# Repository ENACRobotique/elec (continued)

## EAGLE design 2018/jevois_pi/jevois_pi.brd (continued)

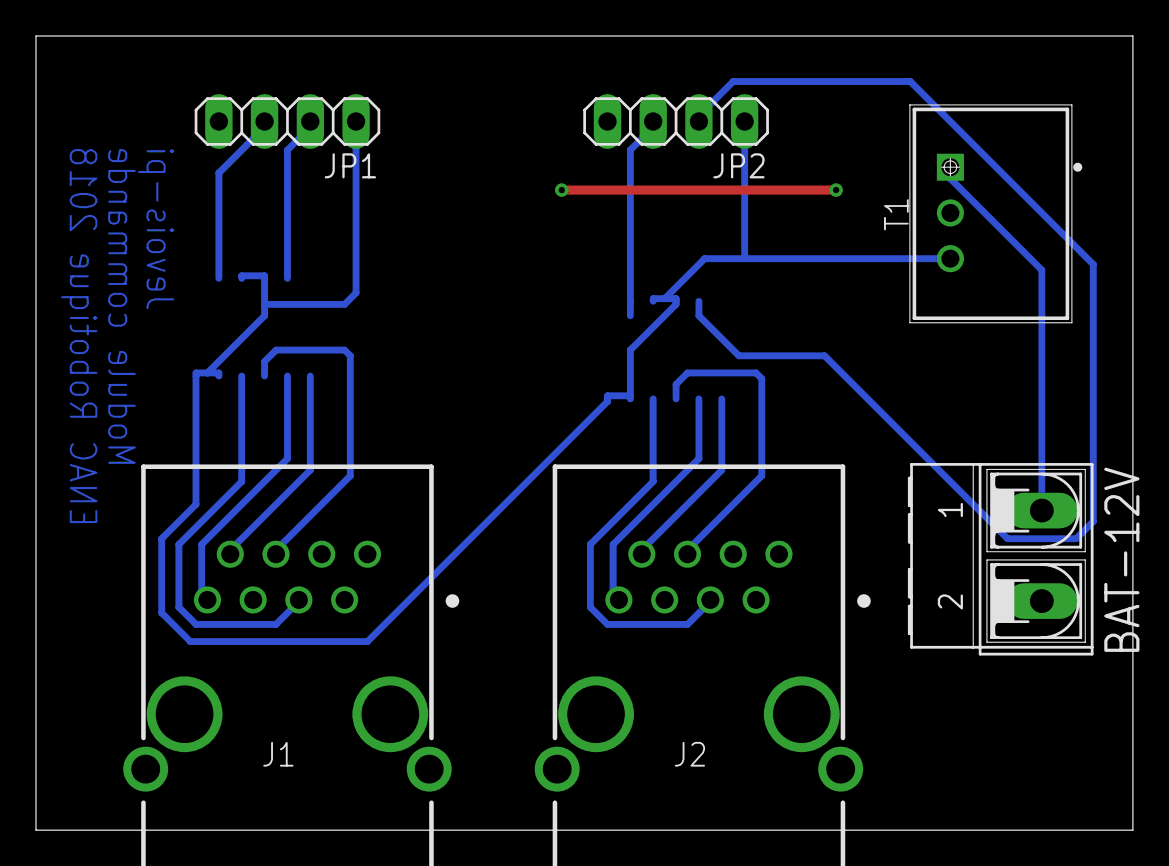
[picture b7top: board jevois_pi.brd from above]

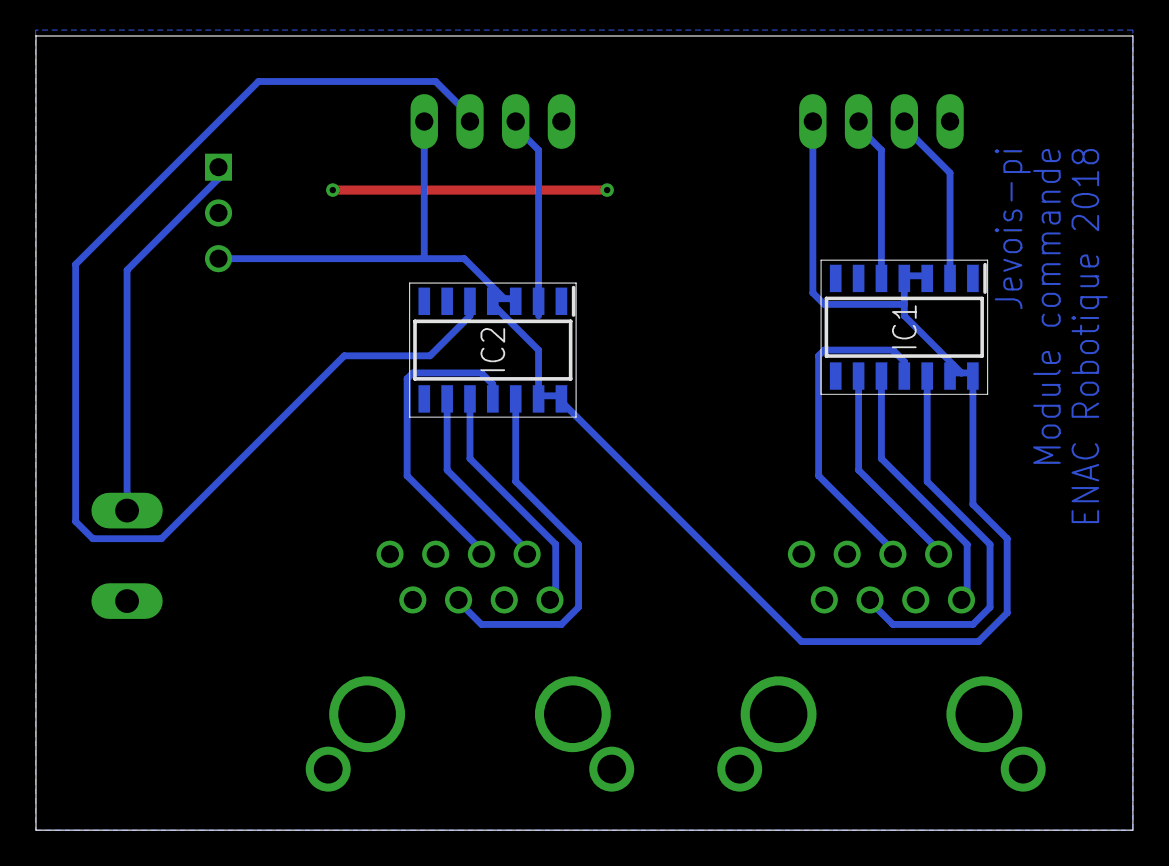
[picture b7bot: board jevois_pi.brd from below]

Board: 2 copper layers, 60.9 x 44.1 mm, 8 parts (2 on the bottom side), 15 nets.

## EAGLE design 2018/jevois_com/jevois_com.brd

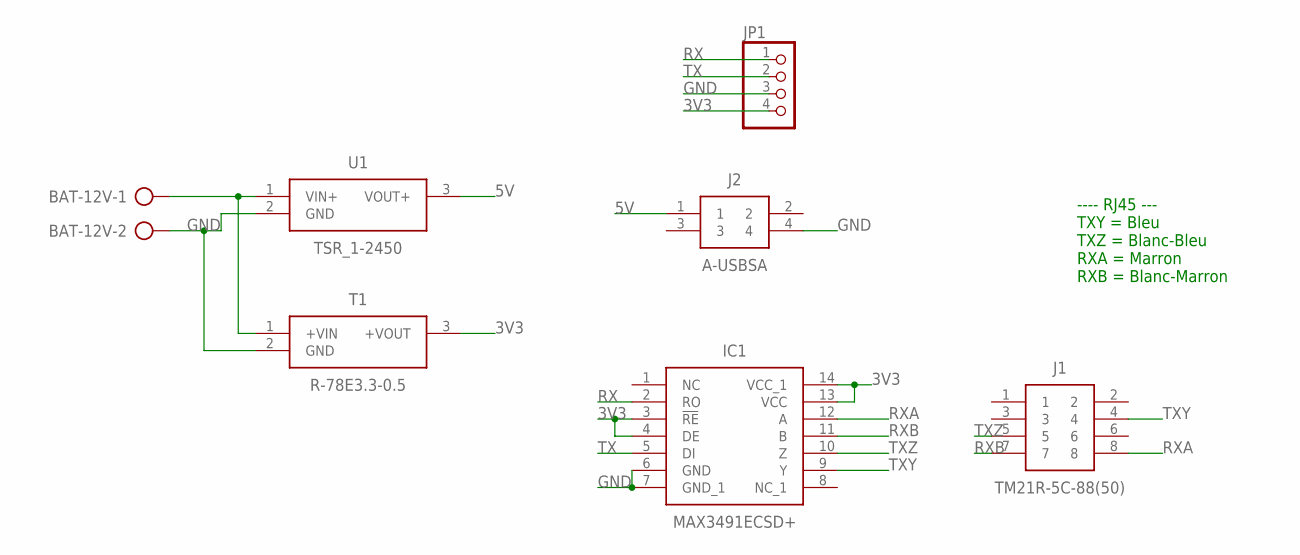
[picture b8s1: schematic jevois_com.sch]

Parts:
BAT-12V: AK500/2-H
IC1: MAX3491ECSD+; SOIC127P600X175-14N
J1: TM21R-5C-88(50)
J2: A-USBSA
JP1: PINHD-1X4; 1X04
T1: R-78E3.3-0.5; SHDRV3W100P0_254_1X3_1160X850X
U1: TSR_1-2450; TSR-1-24120

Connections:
3V3: IC1.3 (!RE), IC1.4 (DE), IC1.13 (VCC), IC1.14 (VCC_1), JP1.4, T1.3 (+VOUT)
5V: J2.1, U1.3 (VOUT+)
GND: BAT-12V.2, IC1.6 (GND), IC1.7 (GND_1), J2.4, JP1.3, T1.2 (GND), U1.2 (GND)
unnamed: BAT-12V.1, T1.1 (+VIN), U1.1 (VIN+)
RX: IC1.2 (RO), JP1.1
RXA: IC1.12 (A), J1.8
RXB: IC1.11 (B), J1.7
TX: IC1.5 (DI), JP1.2
TXY: IC1.9 (Y), J1.4
TXZ: IC1.10 (Z), J1.5

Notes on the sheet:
---- RJ45 --- TXY = Bleu TXZ = Blanc-Bleu RXA = Marron RXB = Blanc-Marron

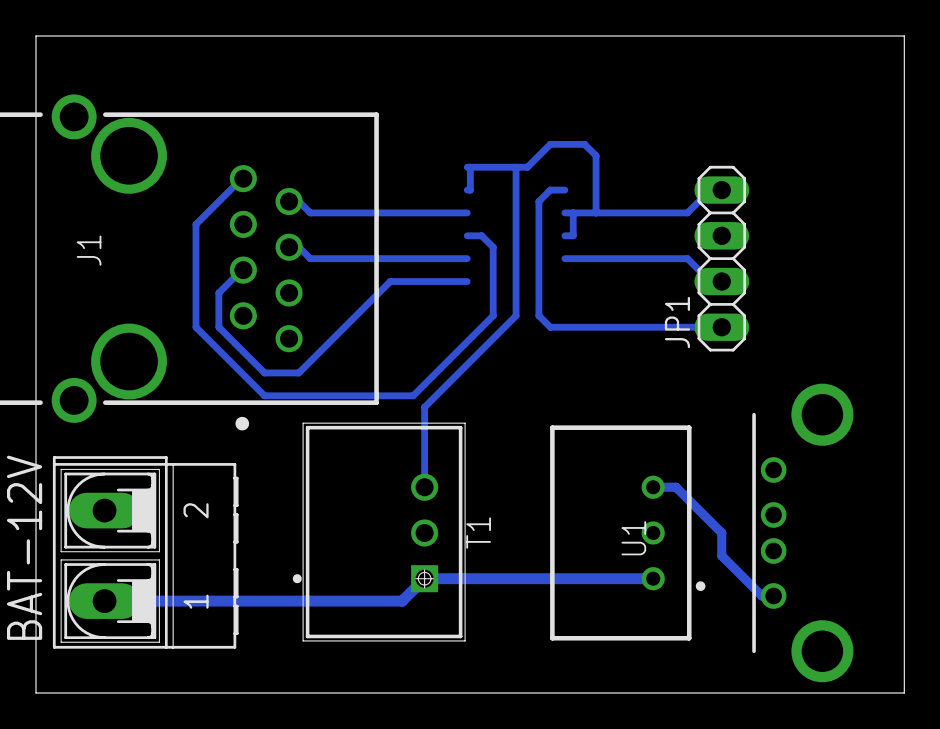
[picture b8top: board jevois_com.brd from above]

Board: 2 copper layers, 48.2 x 36.5 mm, 7 parts (1 on the bottom side), 10 nets.

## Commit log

2015-03-24 [primary_robot] Adds AI/IO board
2015-03-24 [primary_robot] Adds control + power boards Rev1
2015-03-24 [prop_tripod] Updates to pre-Rev2
2015-03-24 [prop-tripod] Update the footprint of the LPC, increase the readability of some name on the board
2015-03-25 [secondary_robot] Adds shematics and board
2015-03-25 [tester] adds shematics and board
2015-03-25 [secondary & tester] remove useless files and move bad located files
2015-03-27 [prop_tripod] Fixes RST connection
2015-04-01 [prop_tripod] Fixes buffer pull-ups + I²C pull-ups headers
2015-04-01 [prop_tripod] Removes useless buffer
2015-04-02 [prop_tripod] Changes pin asssignation
2015-04-03 [tester] add VCC pin for UART
2015-04-03 [tester] create ihm board
2015-04-04 [Programmer ICSP Atmega328p]
2015-04-04 [Programmer ICSP Atmega328p] smaller design
2015-04-04 Add gitignore to ignore .b#, .s#, pdf & epf files. Usefull for everyone.
2015-04-08 [Programmer ICSP Atmega328p] optimise routing
2015-04-08 [tester]move holes to make a good design
2015-04-14 [primary_robot] Adds C2014 R1 Arduino IO shield
2015-04-14 [priom/io] Updates some labels
2015-04-23 [primary_robot] Fixes Uart2 to Uart1 on the BBB
2015-05-05 [2014] Adds 2014 main elec
2015-05-17 [tester] modify to V2 Alpha.
2015-05-17 [tester] improve V2.
2015-05-17 [tester] add pins correspondance.
2015-05-18 [tester] add "pont diviseur" and some modification.
2015-05-21 [Arduino_like] add arduino like board.
2015-05-21 [Arduino_like] modify board.
2015-05-21 [Arduino_like] adds GND, VCC and AREF pins.
2015-05-31 [Arduino like] move on 0.1 inch grid.
2015-06-01 [Arduino like] align pins.
2015-06-01 [Arduino_like] align power.
2015-06-01 [arduino like] move via.
2015-06-01 [Arduino_like] add reset pin.
2015-06-01 [Arduino_like] move text.
2015-06-02 [Tester] new design.
2015-06-02 [tester] continue new design.
2015-06-02 [Arduino_like] change some dimensions.
2015-06-02 [tester] improve design.
2015-06-03 [Arduino_like] V0.1a
2015-06-03 [tester] V2.0a
2015-06-17 [Arduino_like] move labels to the right place.
2015-10-29 [Multitask attiny85] initial commit.
2015-10-29 [tester] modify pin configuration.
2015-10-30 [tester] Begin new design.
2015-10-30 [tester] finish design V3.
2015-10-30 [tester] improve 3rd design.
2015-10-30 [tester] add some measures.
2015-11-02 [tester] puts some wire in top.
2015-11-02 [tester] optimize some routes.
2015-11-02 [tester] keep separation between components.
2015-11-02 [tester] separate some vias.
2015-11-02 [tester] separate other routes.
2015-11-02 [Programmer ICSP Atmega328p] add capa values.
2015-11-03 [elec aiio] Adds a library with raspberry component
2015-11-03 [elec AIIO] Updates the old AIIO card to match the 2016 requirements, rasperry socket, IHM on ard, bluetooth socket on ard and 5 switch plugs on ard.
2016-02-11 [AIIO] Adds a reset button for the Raspi
2016-02-13 [AIIO_board] Add I2C bus "I2C0" for sonar sensors on shematic file.
2016-02-14 [AIIO board] Remove old .brd and .sch files.
2016-02-14 [AIIO boards] Put files in directories wrt the year.
2016-02-14 [AIIO_boards] Create and add components for IHM_BOARD.
2016-02-15 [AIIO_boards] Clean schematic and board files.
2016-02-15 [AIIO_boards] Update footprint of stage 4.
2016-02-15 [AIIO_board]Place connectors for sonar connectors.
2016-02-15 [AIIO_board]Place RP2 and make corrections on I2C_RP2 bus.
2016-02-16 [AIIO_boards] Connect servo connectors to PCA9685PW.
2016-02-16 [AIIO_board] Make route for sonar I2C
2016-02-16 [AIIO_board] Update pin Ardu
2016-02-16 [AIIO_boards] Route presence connectors.
2016-02-17 [AIIO_boars] Update footprint primary.
2016-02-17 [AIIO_board] Add I2C and UART connectors to Arduino and RP2 boards.
2016-02-17 [AIIO_boards] Add connectors for 5v_SIG and root them.
2016-02-17 [AIIO_board] Route IHM components.
2016-02-18 [AIIO_board] Add 3v3 reglator and connectors on .sch and .board files.
2016-02-21 [AIIO_board] Add button and connector for IHM. Remove useless pull-up resistors.
2016-02-22 [AIIO_board] Update personnal library for primary.
2016-02-22 [AIIO_board] Make correction on .brd file to avoid collsions btw parts.
2016-03-16 [AIIO boards] Make corrections, add components (board) for PCA9685.
2016-03-16 [Arm board] Add board for robotic arm.
2016-03-16 Add example file for CAM Processing (Gerber format).
2016-04-13 [AIIO 2016] Corrects a mistake (5V passing through Arduino A0)
2016-04-24 [Porgrammer ICSP] Make another design for handle Attiny85
2016-04-24 [Programmer ICSP] Add awesome eagle!
2016-09-07 [Programmer ICSP] Really add the eagle.
2016-09-07 [Color sensor] Add first version of color sensor.
2017-04-24 [primary] First 2017 commit.
2017-04-24 cleaning
2017-04-24 [Primary] Erase some componants.
2017-04-24 [primary] connectors board RPi.
2017-04-25 [primary] 2nd version, without mass plane.
2017-04-25 [primary] Adds mass plane.
2017-05-04 [RSPI] Adds schematic
2017-09-29 [Smarties_sorter] Adds schematic and board
2017-09-29 [Smarties_sorter] Adds flyback diode
2017-09-29 [Smarties Sorter] Adds a buck
2017-09-29 [Smarties sorter] Adds screw clamp for battery
2017-09-29 [Smarties Sorter] Adds ground plane.
2017-09-30 [Smarties Sorter] Connects AVCC to 5V + capacitor
2017-10-02 [Smarties_sorter] Change color sensor plug
2017-10-02 [Smarties_sorter] Adds resistor to pull down motor command
2017-10-02 [smarties_sorter] Adds UART plug
2017-10-02 [smarties_sorter] Adds capa on the motor
2017-10-02 [smarties_sorter] Change buck to ls7805 and route everything.
2017-10-06 [libraries] Move libraries to better named directory.
2017-10-06 [Multitask attiny85] Reduce wire width.
2017-10-27 [FAT board] Add schematic file.
2017-10-27 [FAT board] Add readme file.
2017-10-27 [FAT board] Modify specs a bit.
2017-10-27 [FAT board] Adds connector for free pins.
2017-10-27 [libraries] Adds 'diy-modules' library.
2017-10-27 [FAT board] Adds reset button.
2017-10-27 [FAT board] Adds necessary components for H-bridges.
2017-10-27 [FAT board] Change some names.
2017-10-27 [FAT board] Adds UART and I2C connectors.
2017-10-27 [FAT board] Connect motors to teensy and add dynamixel control.
2017-10-27 [FAT board] Adds power supply.
2017-10-27 [FAT board] Begin board.
2017-10-27 [primary] Adds label.
2017-10-27 [TRR] Adds board file.
2017-10-27 [TRR] Adds schematic for the car, TRR 2017.
2017-11-01 Add elec boards for primary robot.
2017-11-01 Complete previous commit.
2017-11-02 [FAT board] Connect additionnal power connectors behind interruptors.
2017-11-03 [FAT board] Route board.
2017-11-04 [FAT board] Correct shematic according to Melvin's comments.
2017-11-04 [FAT board] Modify board to match shematic correction.
2017-11-04 [FAT board] Adds some labels.
2017-11-04 Changed I2C Pull-Up resistor selector to match I2C specifications
    Note: I2C Resistors doesn't have any value yet. Assessment of line
    capacitance is in progress...
2017-11-05 Updated I2C ports and pull-up system to match I2C standard specifications
    Note : Assessment of Pull-Up resistors values is still pending.
2017-11-05 Simplified i2c pull-up selector and Partial routing (77%)
2017-11-06 Finished wiring using top layer jumpers
2017-11-07 Adding board Design Rules
2017-11-08 robot_base.sch/brd: routing complete, clearance increased and checked. Add teensy package with bigger pads.
2017-11-08 Change shape of the pads in a new package version of teensy
2017-11-08 Change shape of the pads for D24V50F5 (buck 5V)
2017-11-08 Update robot_system.sch/brd: Minor corrections in sch and start to route.
2017-11-09 Update and complete routing of robot_system board. Last checks TODO.
2017-11-16 Correction of traces Overlap issues
2017-11-23 [robot_base] Update robot_base and robot_systems boards.
2017-11-23 [robot_base] Update dimensions of robot_base board
2017-12-07 [robot_system] Increase clearance, update package of one condo
2017-12-07 [robot_base] Increase clearance
2017-12-10 [robot_base] Update clearance to 15 mil for wire, pad and via.
2017-12-10 [robot_base] Increase clearance. Better routing.
2017-12-11 Updated DRC file to current rules
2018-01-11 Adding Jevois Module transmission board + schematic
    To be set up on the remote modules
2018-01-11 Adding jevois command module and finishing boards
2018-01-11 Correcting a mismatch between input pins
2018-02-20 Adds librairies.
2018-02-20 [FAT pannal] Adds shematic and board.
2018-02-20 [FAT pannal] Split cavalier in two.
2018-02-21 [FAT pannal] Begins routing.
2018-02-21 [FAT pannal] Continue routing.
2018-02-22 [FAT pannal] Finish board V1.
2018-02-22 [FAT pannal] Adds pdfs.
2018-03-06 [dynamixel board] Adds dynamixel board V1.
2018-03-06 [FAT V2]Begin schematic
2018-03-12 [FAT] begins V2
2018-03-12 [Secondary] Adds the board.
2018-03-12 [secondary] Adds the final board
2018-03-12 [Secondary] Begining of the secondary elec card 2018
2018-03-12 [secondary 2018] Modificates the position of the elements above the x abscisse
2018-03-12 [Secondary] Finishes the 2018 schematic
2018-03-12 [secondary] Adds the final schematic and board
2018-03-12 [Libraries] Adds pth08080
2018-03-13 [FAT V2] Route easy side.
2018-03-13 [FAT V2] Finish board.
2018-10-05 Debut test motor control
2019-04-07 [principal2019] Footprint libs.
2019-04-07 [principal2019] Symbol libs.
2019-04-07 [principal2019] 3d packages.
2019-04-07 [principal2019] Adds project.
2019-04-08 [principal2019] Assigns footprints.
2019-04-10 [principal2019] End of elec.
2019-04-10 [principal2019] Adds lib.
2019-04-10 [principal2019] file .pro
2019-04-10 Adds credentials and PDF.
2020-02-12 Begins elec 2020 robot A.
2020-02-14 Updates elec RobotA2020.
2020-02-19 Adds phare2020 elec.
2020-02-27 finish schematic PCA9685 and robotA
2020-03-06 routing carte_PCA9685
2020-03-08 Correction cartes 2020 robotA
2020-03-12 Fin carte elec 2020 robot-a
2020-09-20 init folder and main card
    add folder for main card and kicad libs
2022-11-26 début carte alim v2
2022-11-26 CarteAlimV2-Suite et fin
2022-11-26 Ajout des libraries de logo
2023-02-02 Ajout des cartes de 2022 + début carte principale 2023
2023-02-02 Ajout de labels sur le schématique, tome1
2023-02-03 Ajout des drivers de steppers + connecté tous les tags
2023-02-08 Schéma carte principale fini
2023-02-08 Ajout de résistances de pullup
2023-02-11 Ajout de la carte du panier
2023-02-16 Suppression d'une carte foireuse
2023-02-16 Carte d'alim V2.5
2023-02-16 Arrondi d'une dernière piste
2023-02-16 arrondis ++
2023-02-16 MAJ cartes elec
2023-02-16 Update finale
2023-02-16 Fin de l'elec
2023-02-27 WARNING ENCODER 1
2025-01-30 [pami 2025] Fin PCB V1
2025-03-14 hub CAN
2025-03-17 Hub CAN WIp
2025-10-17 hub smart servos
2025-10-17 useless box 2025
2025-10-17 schemas FTDI
2025-12-11 [PAMI 2026] Schematics + board.
2025-12-12 [PAMI 2026] Add IMU.
2025-12-13 Pompe SAP
2025-12-18 [usb2uart] Fin de la carte
2025-12-18 [SPS6V-5V-5A] Ajout carte Alim 5V
2026-01-02 [pompe SAP] Ajoute UART debug test points and LED.
2026-01-02 [pompe SAP] panel stencil
2026-01-02 [alim 5V] remplace vias par footprint.
